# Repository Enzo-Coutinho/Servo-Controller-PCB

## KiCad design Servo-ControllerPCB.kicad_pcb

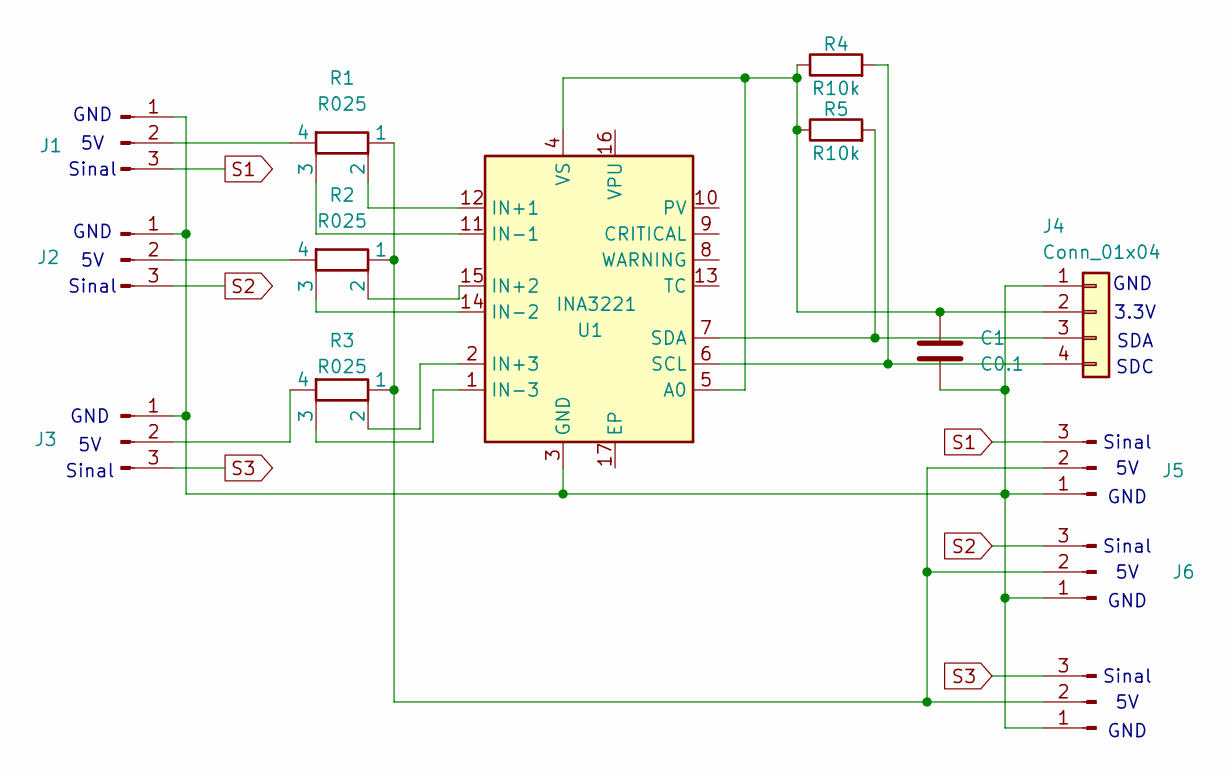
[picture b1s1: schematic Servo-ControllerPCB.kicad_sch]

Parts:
C1: C0.1; C_0805_2012Metric
J1, J2, J3: Conn_01x03_Pin; PinHeader_1x03_P2.54mm_Horizontal
J4: Conn_01x04; JST_PH_B4B-PH-K_1x04_P2.00mm_Vertical
J5, J6, J7: Conn_01x03_Pin; PinSocket_1x03_P2.54mm_Horizontal
R1, R2, R3: R025; R_Shunt_Ohmite_LVK12
R4, R5: R10k; R_0805_2012Metric_Pad1.20x1.40mm_HandSolder
U1: INA3221; Texas_RGV0016A_VQFN-16-1EP_4x4mm_P0.65mm_EP2.1x2.1mm

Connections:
unnamed: C1.2, J1.1, J2.1, J3.1, J4.1, J5.1, J6.1, J7.1, U1.3 (GND)
unnamed: J1.2, R1.4
unnamed: J2.2, R2.4
unnamed: J3.2, R3.4
unnamed: C1.1, J4.2, R4.1, R5.1, U1.4 (VS), U1.5 (A0)
unnamed: J4.3, R5.2, U1.7 (SDA)
unnamed: J4.4, R4.2, U1.6 (SCL)
unnamed: J5.2, J6.2, J7.2, R1.1, R2.1, R3.1
unnamed: R1.2, U1.12 (IN+1)
unnamed: R2.2, U1.15 (IN+2)
unnamed: R3.2, U1.2 (IN+3)
unnamed: R1.3, U1.11 (IN-1)
unnamed: R2.3, U1.14 (IN-2)
unnamed: R3.3, U1.1 (IN-3)
S1: J1.3, J5.3
S2: J2.3, J6.3
S3: J3.3, J7.3

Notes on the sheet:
SDC
SDA
3.3V
Sinal
GND

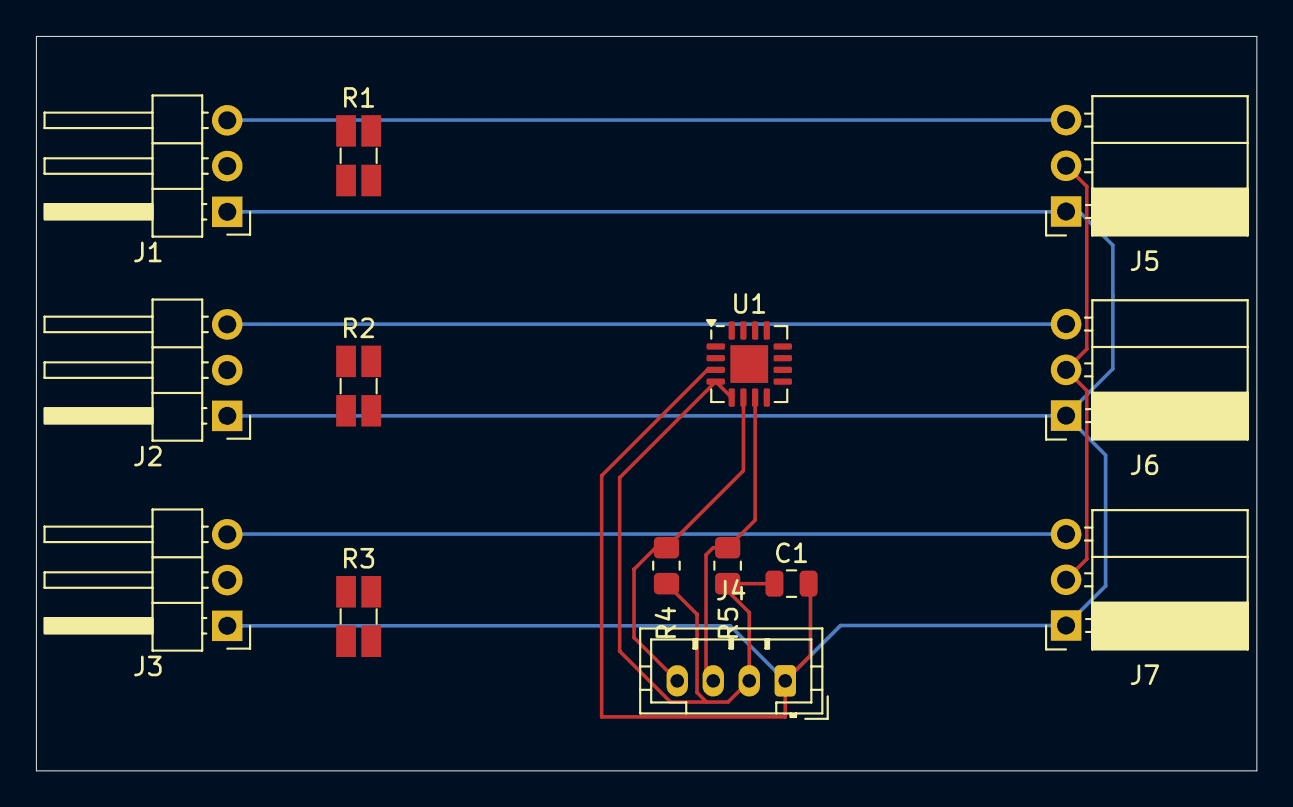
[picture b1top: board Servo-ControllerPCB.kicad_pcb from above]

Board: 2 copper layers, 67.8 x 40.8 mm, 14 parts (0 on the bottom side), 17 nets.

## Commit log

2025-08-19 add files
2025-08-20 feat: first layout
2025-08-20 fix: put jumpers
2025-08-20 fix: change jumper to 2.54
2025-08-20 save
2025-08-21 fix footprints and connectors
2025-08-21 fix: struct of board
2025-08-22 add capacitor
2025-08-22 fix trails
2025-08-22 sabe
2025-08-22 save backup
